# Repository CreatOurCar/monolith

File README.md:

# monolith

DIY data logging platform for Student Formula and Baja: ESP32-S3 firmware records sensors straight to an SD card, and recorded logs are analyzed on the external upstream site (https://v2.monolith.luftaquila.io/).

## Development Environment

- **Required ESP-IDF version: v6.0.1**
- Verify with `idf.py --version` before building.
- **Building with a different version may break the firmware — always use v6.0.1.**

## Features

* 💾 Firmware logs straight to SD — no WiFi, no server, no live telemetry link
   * GPS (NMEA GPRMC) sets the wall clock so recorded logs carry correct absolute time
   * Recorded `.log` files are analyzed on the external upstream site: https://v2.monolith.luftaquila.io/

* 📀 Up to 100 Hz data rate with various signals
   * 1x CAN 2.0(A/B)
   * 1x External GPS
   * 1x Internal 6-axis Accelerometer & Gyroscope
   * 4x Digital input channels
   * 8x Analog input channels

* 🍺 Fully Open-source & Open-hardware under the Beerware license

## Documentation

[Full documentation](https://github.com/CreatOurCar/monolith/tree/main/docs) for DIY and usage details.

## Others

The name of the project was inspired by Arthur C. Clark's novel `2001: A Space Odyssey`.

## Sponsors

### Individuals

<!-- sponsors --><!-- sponsors -->

## LICENSE

For non-commercial use only:

```
"THE BEERWARE LICENSE" (Revision 42):
LUFT-AQUILA wrote this project. As long as you retain this notice,
you can do whatever you want with this stuff. If we meet someday,
and you think this stuff is worth it, you can buy me a beer in return.
```

<br>

<picture>
  <source media="(prefers-color-scheme: dark)" srcset="https://api.star-history.com/svg?repos=CreatOurCar/monolith&type=Date&theme=dark" />
  <source media="(prefers-color-scheme: light)" srcset="https://api.star-history.com/svg?repos=CreatOurCar/monolith&type=Date" />
  
</picture>

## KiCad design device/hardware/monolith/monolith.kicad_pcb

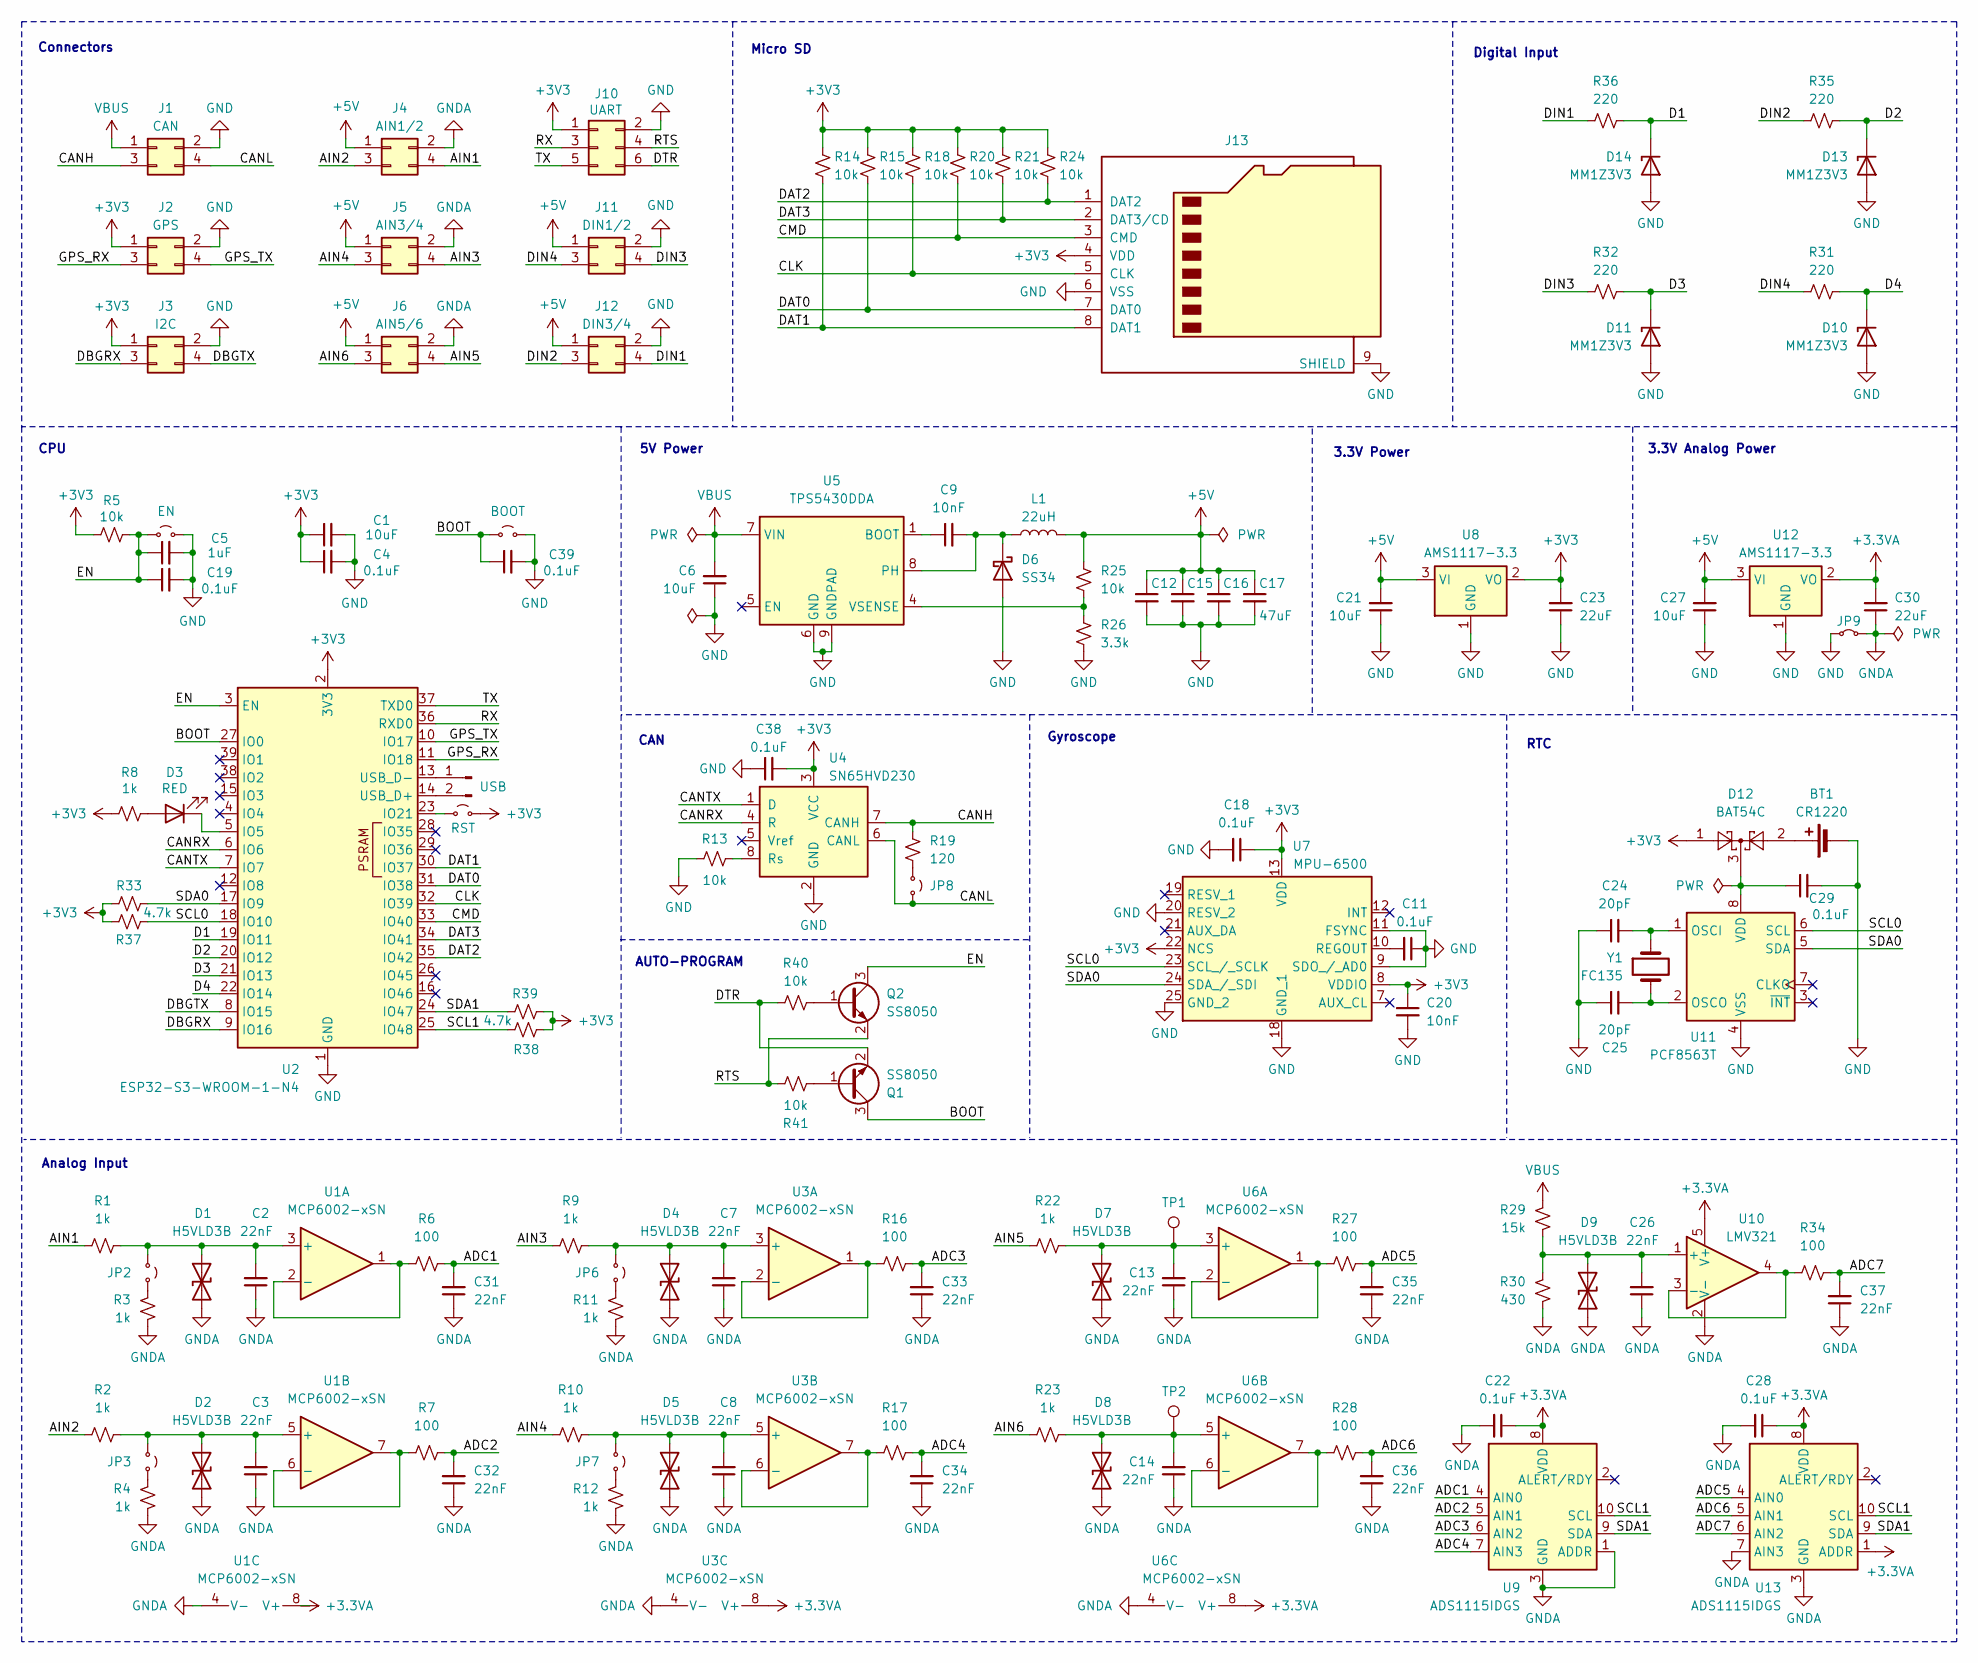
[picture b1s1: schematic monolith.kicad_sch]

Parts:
BT1: CR1220; S8411-45R_1; Manufacturer_Part_Number CR1220-2; LCSC C70381
C1, C21, C27: 10uF; C_0603_1608Metric; LCSC C19702
C2, C3, C7, C8, C13, C14, C26, C31, C32, C33, C34, C35, C36, C37: 22nF; C_0603_1608Metric; LCSC C21122
C4, C11, C18, C19, C22, C28, C29, C38, C39: 0.1uF; C_0603_1608Metric; LCSC C14663
C5: 1uF; C_0603_1608Metric; LCSC C15849
C6: 10uF; C_1206_3216Metric; LCSC C13585
C9, C20: 10nF; C_0603_1608Metric; LCSC C57112
C12, C15, C16, C17: 47uF; C_1206_3216Metric; LCSC C96123
C23, C30: 22uF; C_0603_1608Metric; LCSC C59461
C24, C25: 20pF; C_0603_1608Metric; LCSC C1648
D1, D2, D4, D5, D7, D8, D9: H5VLD3B; D_SOD-323; LCSC C20615805
D3: RED; LED_0603_1608Metric; LCSC C2286
D6: SS34; D_SMA; LCSC C8678
D10, D11, D13, D14: MM1Z3V3; D_SOD-123; LCSC C22379456
D12: BAT54C; SOT-23; Manufacturer_Part_Number BAT54C; LCSC C37704
J1: CAN; Molex_Mini-Fit_Jr_5569-04A2_2x02_P4.20mm_Horizontal
J2: GPS; Molex_Mini-Fit_Jr_5569-04A2_2x02_P4.20mm_Horizontal
J3: I2C; Molex_Mini-Fit_Jr_5569-04A2_2x02_P4.20mm_Horizontal
J4: AIN1/2; Molex_Mini-Fit_Jr_5569-04A2_2x02_P4.20mm_Horizontal
J5: AIN3/4; Molex_Mini-Fit_Jr_5569-04A2_2x02_P4.20mm_Horizontal
J6: AIN5/6; Molex_Mini-Fit_Jr_5569-04A2_2x02_P4.20mm_Horizontal
J7: USB; PinHeader_1x02_P1.00mm_Vertical
J10: UART; PinHeader_2x03_P2.54mm_Vertical
J11: DIN1/2; Molex_Mini-Fit_Jr_5569-04A2_2x02_P4.20mm_Horizontal
J12: DIN3/4; Molex_Mini-Fit_Jr_5569-04A2_2x02_P4.20mm_Horizontal
J13: Micro_SD_Card; TF115BCP9; LCSC C393941
JP1: EN; PinHeader_1x02_P1.00mm_Vertical
JP2, JP3, JP6, JP7: Jumper_2_Small_Open; PinHeader_1x02_P2.54mm_Vertical
JP4: BOOT; PinHeader_1x02_P1.00mm_Vertical
JP5: RST; PinHeader_1x02_P2.54mm_Vertical
JP8: CAN 120Ω; PinHeader_1x02_P2.54mm_Vertical
JP9: Jumper_2_Small_Bridged; SolderJumper-2_P1.3mm_Bridged_RoundedPad1.0x1.5mm
L1: 22uH; L_Sunlord_MWSA0603S; LCSC C177244
Q1, Q2: SS8050; SOT-23; LCSC C2150
R1, R2, R3, R4, R8, R9, R10, R11, R12, R22, R23: 1k; R_0603_1608Metric; LCSC C21190
R5, R13, R14, R15, R18, R20, R21, R24, R25, R40, R41: 10k; R_0603_1608Metric; LCSC C25804
R6, R7, R16, R17, R27, R28, R34: 100; R_0603_1608Metric; LCSC C22775
R19: 120; R_0603_1608Metric; LCSC C22787
R26: 3.3k; R_0603_1608Metric; LCSC C22978
R29: 15k; R_0603_1608Metric; LCSC C22809
R30: 430; R_0603_1608Metric; LCSC C23170
R31, R32, R35, R36: 220; R_0603_1608Metric; LCSC C22962
R33, R37, R38, R39: 4.7k; R_0603_1608Metric; LCSC C23162
TP1, TP2: TestPoint; PinHeader_1x01_P1.00mm_Vertical
U1, U3, U6: MCP6002-xSN; SOIC-8_3.9x4.9mm_P1.27mm; LCSC C7377
U2: ESP32-S3-WROOM-1-N4; ESP32-S3-WROOM-1; LCSC C2913197
U4: SN65HVD230; SOIC-8_3.9x4.9mm_P1.27mm; LCSC C12084
U5: TPS5430DDA; TI_SO-PowerPAD-8_ThermalVias; LCSC C9864
U7: MPU-6500; QFN40P300X300X95-25N-D; Manufacturer_Part_Number MPU-6500; Mouser Part Number 410-MPU-6500
U8, U12: AMS1117-3.3; SOT-223-3_TabPin2; LCSC C6186
U9, U13: ADS1115IDGS; TSSOP-10_3x3mm_P0.5mm; LCSC C37593
U10: LMV321; SOT-23-5; LCSC C7972
U11: PCF8563T; SOIC-8_3.9x4.9mm_P1.27mm; LCSC C7440
Y1: FC135; Crystal_SMD_3215-2Pin_3.2x1.5mm; LCSC C32346

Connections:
+3.3VA: C22.1, C28.1, C30.2, U1.8 (V+), U3.8 (V+), U6.8 (V+), U9.8 (VDD), U10.5 (V+), U12.2 (VO), U13.1 (ADDR), U13.8 (VDD)
+3V3: C1.1, C4.1, C18.1, C20.1, C23.2, C38.2, D12.1, J2.1, J3.1, J10.1, J13.4 (VDD), JP5.2 (B), R5.2, R8.1, R14.2, R15.2, R18.2, R20.2, R21.2, R24.2, R33.1, R37.2, R38.1, R39.2, U2.2 (3V3), U4.3 (VCC), U7.8 (VDDIO), U7.13 (VDD), U7.22 (NCS), U8.2 (VO)
+5V: C12.1, C15.1, C16.1, C17.1, C21.2, C27.2, J4.1, J5.1, J6.1, J11.1, J12.1, L1.2, R25.2, U8.3 (VI), U12.3 (VI)
/ADC1: C31.2, R6.2, U9.4 (AIN0)
/ADC2: C32.2, R7.2, U9.5 (AIN1)
/ADC3: C33.2, R16.2, U9.6 (AIN2)
/ADC4: C34.2, R17.2, U9.7 (AIN3)
/ADC5: C35.2, R27.2, U13.4 (AIN0)
/ADC6: C36.2, R28.2, U13.5 (AIN1)
/ADC7: C37.2, R34.2, U13.6 (AIN2)
/AIN1: J4.4, R1.1
/AIN2: J4.3, R2.1
/AIN3: J5.4, R9.1
/AIN4: J5.3, R10.1
/AIN5: J6.4, R22.1
/AIN6: J6.3, R23.1
/BOOT: C39.1, JP4.1 (A), Q1.3 (C), U2.27 (IO0)
/CANH: J1.3, R19.2, U4.7 (CANH)
/CANL: J1.4, JP8.2 (B), U4.6 (CANL)
/CANRX: U2.6 (IO6), U4.4 (R)
/CANTX: U2.7 (IO7), U4.1 (D)
/CLK: J13.5 (CLK), R18.1, U2.32 (IO39)
/CMD: J13.3 (CMD), R20.1, U2.33 (IO40)
/D1: D14.1 (K), R36.2, U2.19 (IO11)
/D2: D13.1 (K), R35.2, U2.20 (IO12)
/D3: D11.1 (K), R32.2, U2.21 (IO13)
/D4: D10.1 (K), R31.2, U2.22 (IO14)
/DAT0: J13.7 (DAT0), R15.1, U2.31 (IO38)
/DAT1: J13.8 (DAT1), R14.1, U2.30 (IO37)
/DAT2: J13.1 (DAT2), R24.1, U2.35 (IO42)
/DAT3: J13.2 (DAT3/CD), R21.1, U2.34 (IO41)
/DBGRX: J3.3, U2.9 (IO16)
/DBGTX: J3.4, U2.8 (IO15)
/DIN1: J12.4, R36.1
/DIN2: J12.3, R35.1
/DIN3: J11.4, R32.1
/DIN4: J11.3, R31.1
/DTR: J10.6, Q1.2 (E), R40.1
/EN: C5.1, C19.1, JP1.1 (A), Q2.3 (C), R5.1, U2.3 (EN)
/GPS_RX: J2.3, U2.11 (IO18)
/GPS_TX: J2.4, U2.10 (IO17)
/RTS: J10.4, Q2.2 (E), R41.2
/RX: J10.3, U2.36 (RXD0)
/SCL0: R37.1, U2.18 (IO10), U7.23 (SCL_/_SCLK), U11.6 (SCL)
/SCL1: R38.2, U2.25 (IO48), U9.10 (SCL), U13.10 (SCL)
/SDA0: R33.2, U2.17 (IO9), U7.24 (SDA_/_SDI), U11.5 (SDA)
/SDA1: R39.1, U2.24 (IO47), U9.9 (SDA), U13.9 (SDA)
/TX: J10.5, U2.37 (TXD0)
GND: BT1.2 (-), C1.2, C4.2, C5.2, C6.1, C11.1, C12.2, C15.2, C16.2, C17.2, C18.2, C19.2, C20.2, C21.1, C23.1, C24.1, C25.1, C27.1, C29.2, C38.1, C39.2, D6.2 (A), D10.2 (A), D11.2 (A), D13.2 (A), D14.2 (A), J1.2, J2.2, J3.2, J10.2, J11.2, J12.2, J13.6 (VSS), J13.9 (SHIELD), JP1.2 (B), JP4.2 (B), JP9.1 (A), R13.1, R26.1, U2.1 (GND), U2.40 (GND), U2.41 (GND), U4.2 (GND), U5.6 (GND), U5.9 (GNDPAD), U7.9 (SDO_/_AD0), U7.11 (FSYNC), U7.18 (GND_1), U7.20 (RESV_2), U7.25 (GND_2), U8.1 (GND), U11.4 (VSS), U12.1 (GND)
GNDA: C2.1, C3.1, C7.1, C8.1, C13.1, C14.1, C22.2, C26.1, C28.2, C30.1, C31.1, C32.1, C33.1, C34.1, C35.1, C36.1, C37.1, D1.2 (A2), D2.2 (A2), D4.2 (A2), D5.2 (A2), D7.2 (A2), D8.2 (A2), D9.2 (A2), J4.2, J5.2, J6.2, JP9.2 (B), R3.1, R4.1, R11.1, R12.1, R30.1, U1.4 (V-), U3.4 (V-), U6.4 (V-), U9.1 (ADDR), U9.3 (GND), U10.2 (V-), U13.3 (GND), U13.7 (AIN3)
unnamed: BT1.1 (+), D12.2
unnamed: C2.2, D1.1 (A1), JP2.1 (A), R1.2, U1.3 (+)
unnamed: C3.2, D2.1 (A1), JP3.1 (A), R2.2, U1.5 (+)
unnamed: D3.2 (A), R8.2
unnamed: D3.1 (K), U2.5 (IO5)
unnamed: C7.2, D4.1 (A1), JP6.1 (A), R9.2, U3.3 (+)
unnamed: C8.2, D5.1 (A1), JP7.1 (A), R10.2, U3.5 (+)
unnamed: C9.2, D6.1 (K), L1.1, U5.8 (PH)
unnamed: C13.2, D7.1 (A1), R22.2, TP1.1, U6.3 (+)
unnamed: C14.2, D8.1 (A1), R23.2, TP2.1, U6.5 (+)
unnamed: C26.2, D9.1 (A1), R29.1, R30.2, U10.1 (+)
unnamed: J7.1, U2.13 (USB_D-)
unnamed: J7.2, U2.14 (USB_D+)
unnamed: JP2.2 (B), R3.2
unnamed: JP3.2 (B), R4.2
unnamed: JP5.1 (A), U2.23 (IO21)
unnamed: JP6.2 (B), R11.2
unnamed: JP7.2 (B), R12.2
unnamed: JP8.1 (A), R19.1
unnamed: Q1.1 (B), R41.1
unnamed: Q2.1 (B), R40.2
unnamed: R6.1, U1.1, U1.2 (-)
unnamed: R7.1, U1.6 (-), U1.7
unnamed: R16.1, U3.1, U3.2 (-)
unnamed: R17.1, U3.6 (-), U3.7
unnamed: R13.2, U4.8 (Rs)
unnamed: C9.1, U5.1 (BOOT)
unnamed: R25.1, R26.2, U5.4 (VSENSE)
unnamed: R27.1, U6.1, U6.2 (-)
unnamed: R28.1, U6.6 (-), U6.7
unnamed: C11.2, U7.10 (REGOUT)
unnamed: R34.1, U10.3 (-), U10.4
unnamed: C24.2, U11.1 (OSCI), Y1.1
unnamed: C25.2, U11.2 (OSCO), Y1.2
unnamed: C29.1, D12.3, U11.8 (VDD)
VBUS: C6.2, J1.1, R29.2, U5.7 (VIN)

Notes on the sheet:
CAN
AUTO-PROGRAM
Analog Input
Micro SD
Digital Input
Connectors
3.3V Power
RTC
3.3V Analog Power
CPU
Gyroscope
5V Power

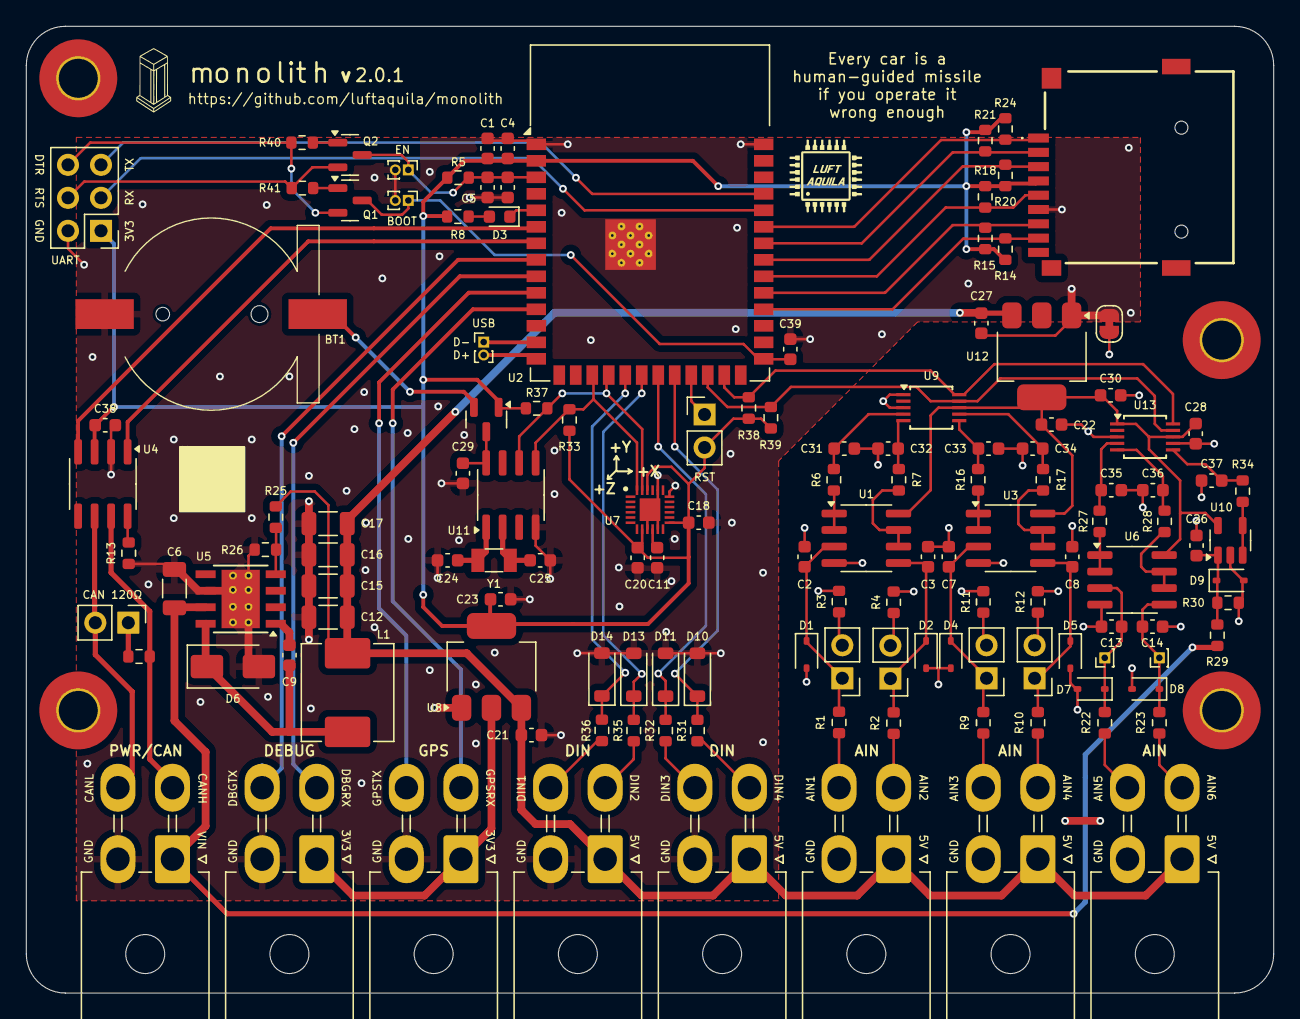
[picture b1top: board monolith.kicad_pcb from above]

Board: 2 copper layers, 96.0 x 74.4 mm, 133 parts (0 on the bottom side), 86 nets.

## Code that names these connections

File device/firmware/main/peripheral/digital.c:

#include "main.h"

#include "driver/gpio.h"

// 기계식 스위치는 한 번 눌러도 접점이 수 ms 동안 수십 번 튕긴다(채터링).
// 엣지마다 그대로 기록하면 로그 큐/SD가 쓰레기 레코드로 넘치므로:
//   ISR   — 마지막 엣지 시각만 남기고 태스크를 깨운다 (기록하지 않음)
//   task  — 버스트 첫 엣지에 즉시 1회 기록(지연 최소화), 이후 신호가
//           DEBOUNCE_QUIET_MS 동안 조용해지면 안정된 최종 상태를 기록
// 기록되는 레코드 자체는 기존과 동일한 4채널 상태 스냅샷 — 로그 형식 불변.
#define DEBOUNCE_QUIET_MS 10

static TaskHandle_t digital_task;
static volatile TickType_t last_edge_tick;  // 1kHz tick == 1ms; 32-bit write is atomic

static void digital_isr(void *arg) {
  last_edge_tick = xTaskGetTickCountFromISR();

  BaseType_t woken = pdFALSE;
  vTaskNotifyGiveFromISR(digital_task, &woken);
  portYIELD_FROM_ISR(woken);
}

/* read all four inputs; log only when the state differs from the last logged one */
static void digital_sample_and_log(bool force) {
  uint32_t din1 = gpio_get_level(GPIO_NUM_11);
  uint32_t din2 = gpio_get_level(GPIO_NUM_12);
  uint32_t din3 = gpio_get_level(GPIO_NUM_13);
  uint32_t din4 = gpio_get_level(GPIO_NUM_14);

  if (!force && logbuf.digital.payload.digital.din1 == din1 && logbuf.digital.payload.digital.din2 == din2 &&
      logbuf.digital.payload.digital.din3 == din3 && logbuf.digital.payload.digital.din4 == din4) {
    return;
  }

  logbuf.digital.payload.digital.din1 = din1;
  logbuf.digital.payload.digital.din2 = din2;
  logbuf.digital.payload.digital.din3 = din3;
  logbuf.digital.payload.digital.din4 = din4;
  LOG(LOG_TYPE_DIGITAL, &logbuf.digital);
}

/*******************************************************************************
 * Digital input interrupt monitor task
 ******************************************************************************/
void task_digital(void *pvParameters) {
  gpio_config_t gpio;

  gpio.pin_bit_mask = (1ULL << GPIO_NUM_11) | (1ULL << GPIO_NUM_12) | (1ULL << GPIO_NUM_13) | (1ULL << GPIO_NUM_14);
  gpio.mode         = GPIO_MODE_INPUT;
  gpio.intr_type    = GPIO_INTR_ANYEDGE;
  gpio.pull_up_en   = GPIO_PULLUP_DISABLE;
  gpio.pull_down_en = GPIO_PULLDOWN_ENABLE;

  if (gpio_config(&gpio) != ESP_OK) {
    ERROR_SYSLOG(&init, DIGITAL, "GPIO init failure", "DGT_INIT_FAIL");
  }

  // record initial state
  digital_sample_and_log(true);

  digital_task = xTaskGetCurrentTaskHandle();

  esp_err_t ret = gpio_isr_handler_add(GPIO_NUM_11, digital_isr, NULL);
  ret |= gpio_isr_handler_add(GPIO_NUM_12, digital_isr, NULL);
  ret |= gpio_isr_handler_add(GPIO_NUM_13, digital_isr, NULL);
  ret |= gpio_isr_handler_add(GPIO_NUM_14, digital_isr, NULL);

  if (ret != ESP_OK) {
    ERROR_SYSLOG(&init, DIGITAL, "GPIO isr install failure", "DGT_ISR_FAIL");
  }

  if (IS_OK(&init, DIGITAL)) {
    CLEAR_ALL(&logbuf.run, DIGITAL);
    SYSLOG("DGT_RDY");
  } else {
    COPY_STATE(&logbuf.run, &init, DIGITAL);
  }

  while (true) {
    ulTaskNotifyTake(pdTRUE, portMAX_DELAY);  // wait for the first edge of a burst

    digital_sample_and_log(false);

    // wait until the inputs have been quiet for DEBOUNCE_QUIET_MS
    while (xTaskGetTickCount() - last_edge_tick < pdMS_TO_TICKS(DEBOUNCE_QUIET_MS)) {
      vTaskDelay(pdMS_TO_TICKS(2));
    }

    // drop notifications accumulated during the burst, then log the settled state.
    // an edge arriving after this take sets the notification again, so the outer
    // loop reruns and no final state change is ever lost.
    ulTaskNotifyTake(pdTRUE, 0);
    digital_sample_and_log(false);
  }
}

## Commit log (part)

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2025-06-02 add: install guide
2025-07-01 add: v2 schematics and footprints
2025-07-01 remove: Rust firmware
2025-07-25 add: initial project
2025-07-25 update: apply beerware for non-commercial use only
2025-07-25 add: ci build workflow
2025-07-25 update: PCB prototype
2025-07-25 add: Makefile and wokwi simulation
2025-07-25 update: idf config options
2025-07-25 add: error handling system and NVS config management
2025-07-25 add: start peripheral tasks by nvs value
2025-07-25 update: I2C2 to I2C0
2025-07-25 add: log protocol
2025-07-25 update: replace MPU-6050 to MPU-6500
2025-07-25 impl: webserver with ap mode
2025-07-25 update: set core clock to 240MHz
2025-07-25 fix: enforce IDF_PATH
2025-07-25 add: log checksum calc and enqueue
2025-07-25 add: basic structure and initializations
2025-07-25 add: logo assets
2025-07-25 fix: misc bugs
2025-07-25 update: prototype PCB
2025-07-25 add: STA mode prototype
2025-07-25 improve: led and logging system
2025-07-25 add: sntp time sync
2025-07-25 impl: mqtt online check with LWT
2025-07-25 improve: embed text files
2025-07-25 fix: set flash size to 4MB for N4
2025-07-25 improve: unify nvs namespace
2025-07-25 update: clang-format PointerAlignment
2025-07-25 improve: make traefik container optional
2025-07-25 impl: SNTP time sync to RTC
2025-07-25 update: set mqtt ACL and authentication
2025-07-25 add: mqtt topic subscription handler structure
2025-07-25 fix: wrong marking TX/RX on the PCB
2025-07-25 update: disable runtime log level checks
2025-07-25 impl: mqtt set commands
2025-07-25 update: set proper ignores
2025-07-25 add: basic server architecture
2025-07-25 fix: wrong LED direction
2025-07-25 update: set hostname and mac on AP name
2025-07-25 add: mqtt prototype
2025-07-25 add: make config
2025-07-25 add: tz info on config
2025-07-25 improve: nvs handling
2025-07-25 update: set coreid as enum
2025-07-25 update: enable QIO, set upload and console baud to 921600
2025-07-25 improve: error state management
2025-07-25 update: set global logbuf and run state
2025-07-25 impl: mqtt cmd ls, del, get
2025-07-25 add: info messages
2025-07-25 update: drop node and set nginx
2025-07-25 improve: add reboot button on html
2025-07-25 update: use synchronous api on i2c transfer
2025-07-25 fix: wait next period on transfer failure too
2025-07-25 add: 1s period mqtt data publish
2025-07-25 improve: quit task after init and make period correct
2025-07-25 remove: wokwi simulation
2025-07-25 impl: analog record
2025-07-25 update: set optimization level to -O2
2025-07-25 fix: state shift bits
2025-07-25 impl: RST button reset NVS
2025-07-25 improve: separate files per peripherals
2025-07-25 fix: record initial digital state
2025-07-25 add: digital input prototype
2025-07-25 impl: CAN message receive
2025-07-25 update: rename evtgrp variables
2025-07-25 fix: sync log to sd card
2025-07-25 fix: ci build
2025-07-25 add: publish syslog to mqtt
2025-07-25 Squashed 'web/' content from commit 23bcf92
    git-subtree-dir: web
    git-subtree-split: 23bcf922ab1826953fc32f85a3b6693a8bce10cc
2025-07-25 update: set frontend template
2025-07-27 update: apply dark theme and purple color
2025-07-27 update: settings page layout
2025-07-27 update: set topbar, default theme and logo
2025-07-27 remove: unused views
2025-07-27 bump: vite
2025-07-27 add: uplot
2025-07-27 update: add sample uplot graph
2025-07-27 update: set style
2025-07-27 update: set responsive chart size sample
2025-07-28 update: set acl file mod
2025-07-28 add: protocol parser prototype
2025-07-28 impl: set NVS via mqtt
2025-07-28 add: refresh button
2025-07-28 update: set keepalive
2025-07-28 update: idf to v5.5
2025-07-29 update: disable retain except boot record
2025-07-29 update: add terminal console
2025-07-29 impl: state telemetry
2025-07-29 add: time tags on state
2025-07-29 update: add uptime and set mqtt rate to 500ms
2025-07-29 fix: client side checksum failure
2025-07-29 impl: usrevt transmit and digital card view
2025-07-30 update: add views setting page
2025-07-30 improve: misc configuration behavior
2025-07-30 update: rename views
2025-07-30 impl: file list and delete
2025-07-30 update: disable cfg publish on mqtt conn
2025-07-31 impl: file download
2025-07-31 fix: send default USREVT on empty send and add ack
2025-07-31 update: view control variable
2025-08-01 impl: analog chart
2025-08-01 impl: gyro chart
2025-08-01 add: current position button
2025-08-01 impl: digital telemetry
2025-08-01 add: map
2025-08-01 update: chart and card styles
2025-08-01 impl: chart dark theme
2025-08-01 update: skip current log file on ls and del/all
2025-08-01 impl: multiple axes with same split range
2025-08-01 update: hide points
2025-08-02 improve: checksum failure during analog measurement
2025-08-02 add: viewer prototype
2025-08-03 impl: load file
2025-08-03 impl: graph viewer
2025-08-04 impl: events
2025-08-04 improve: graph view
2025-08-04 fix: load map on both page
2025-08-05 impl: gps prototype with pattern detection interrupt
2025-08-06 impl: neo6m config cmd
2025-08-06 impl: parse GPRMC message
2025-08-06 impl: parse gps log on web
2025-08-06 impl: telemetry map viewer
2025-08-06 fix: refresh list on delete
2025-08-06 update: add gps speed graph
2025-08-06 impl: gps viewer
2025-08-06 improve: map aspect-ratio
2025-08-06 improve: prevent downloading on other client
2025-08-06 update: drop 115200 bps gps for stability
2025-08-06 improve: gps coord accuracy
2025-08-06 fix: download filtering
2025-08-06 update: map mark colors
2025-08-06 impl: viewer timelapse slider
2025-08-06 improve: add position display
2025-08-06 improve: retry on i2c failure
2025-08-07 update: add download speed measurement, make get ack QOS 1
2025-08-07 update: make slider precise
2025-08-07 update: set analog prio to 6, core affinity to lwip and mqtt task
2025-08-07 improve: gps checksum fail
2025-08-07 update: auto load configuration
2025-08-07 add: display card toggle
2025-08-07 add: unit management
2025-08-07 impl: analog ui config
2025-08-07 update: save views to localStorage
2025-08-08 update: dynamic unit in telemetry
2025-08-08 improve: auto color generator
2025-08-08 improve: generate chart scale from units
2025-08-08 add: loading messages
2025-08-08 fix: usrevt terminating null char
2025-08-09 impl: can decoder
2025-08-09 improve: cardview style
2025-08-09 update: misc styles
2025-08-09 update: add uplot zoom plugins
2025-08-09 improve: set gyro offset registers
2025-08-09 fix: data without gps
2025-08-09 impl: telemetry update interval config
2025-08-10 impl: can receive
2025-08-10 fix: reset gyro offset before calibrate
2025-08-10 impl: can message transmit
2025-08-10 improve: error recovery
2025-08-10 impl: can telemetry graph view
2025-08-10 impl: export cfg
2025-08-10 improve: remove digital value from views
2025-08-11 drop: geolocation button
2025-08-11 improve: gyro error recovery
2025-08-11 impl: import/reset ui cfg
2025-08-11 fix: wrong button operation
2025-08-11 update: npm package name
2025-08-11 fix: docker-compose
2025-08-11 fix: xterm import
2025-08-11 fix: single page application routing
2025-08-11 fix: reset prev alert
2025-08-12 add: white logo
2025-08-12 add: docs template
2025-08-12 update: build firmware only on change at CI
2025-08-12 update: build docs on web build
2025-08-12 fix: docs routing
2025-08-12 impl: viewer can data
2025-08-12 update: full firmware for flashing
2025-08-12 update: remove jumpers
    PCB v2.0.1
2025-08-12 update: docs template
2025-08-12 update: README
2025-08-12 add: workflows
2025-08-14 add: theme license to html
2025-08-18 fix: GPS buffer overflow and add bitrate detection
2025-08-19 add: documentation
2025-08-22 update: disable additional NMEA messages
2025-08-22 update: remove all task core affinities
2025-08-22 improve: read CAN RX fifo more efficiently
2025-08-24 improve: split time slot
2025-08-24 fix: log magic mismatch handling
2025-08-25 impl: CAN id hash table for telemetry
2025-08-25 update: change FreeRTOS ticks to 50 Hz
2025-08-25 update: enlarge log queue length
2025-08-25 update: docs
2025-08-26 update: add mini firmware build
2025-08-27 add: mini hardware
2025-08-28 update: misc pcb changes
2025-08-29 impl: mini analog task
2025-10-20 build(deps-dev): bump vite from 7.0.6 to 7.1.11 in /web
    Bumps [vite](https://github.com/vitejs/vite/tree/HEAD/packages/vite) from 7.0.6 to 7.1.11.
    - [Release notes](https://github.com/vitejs/vite/releases)
    - [Changelog](https://github.com/vitejs/vite/blob/main/packages/vite/CHANGELOG.md)
    - [Commits](https://github.com/vitejs/vite/commits/v7.1.11/packages/vite)
    ---
    updated-dependencies:
2025-11-10 update: readme sponsors
2025-11-10 Deploying to main from @ luftaquila/monolith@65aa01479936febd3e259b5cb4d91d847d5a2b51 🚀
2025-11-10 update: add sponsor review in docs
2026-01-13 fix: release workflow
2026-01-16 add: firmware flashing script
2026-01-16 build(deps-dev): bump js-yaml from 4.1.0 to 4.1.1 in /web
    Bumps [js-yaml](https://github.com/nodeca/js-yaml) from 4.1.0 to 4.1.1.
    - [Changelog](https://github.com/nodeca/js-yaml/blob/master/CHANGELOG.md)
    - [Commits](https://github.com/nodeca/js-yaml/compare/4.1.0...4.1.1)
    ---
    updated-dependencies:
    - dependency-name: js-yaml
2026-01-23 npm update
2026-01-23 bump: npm packages
2026-01-23 update: docs for difference between mini and original
2026-03-20 add: CLAUDE.md
2026-03-20 fix: full nginx config with dynamic DNS, access_log off, asset caching
2026-03-21 build(deps-dev): bump minimatch from 3.1.2 to 3.1.5 in /web
    Bumps [minimatch](https://github.com/isaacs/minimatch) from 3.1.2 to 3.1.5.
    - [Changelog](https://github.com/isaacs/minimatch/blob/main/changelog.md)
    - [Commits](https://github.com/isaacs/minimatch/compare/v3.1.2...v3.1.5)
    ---
    updated-dependencies:
    - dependency-name: minimatch
2026-03-21 build(deps-dev): bump flatted from 3.3.3 to 3.4.2 in /web
    Bumps [flatted](https://github.com/WebReflection/flatted) from 3.3.3 to 3.4.2.
    - [Commits](https://github.com/WebReflection/flatted/compare/v3.3.3...v3.4.2)
    ---
    updated-dependencies:
    - dependency-name: flatted
    dependency-version: 3.4.2
2026-03-26 build(deps): bump picomatch from 4.0.3 to 4.0.4 in /web
    Bumps [picomatch](https://github.com/micromatch/picomatch) from 4.0.3 to 4.0.4.
    - [Release notes](https://github.com/micromatch/picomatch/releases)
    - [Changelog](https://github.com/micromatch/picomatch/blob/master/CHANGELOG.md)
    - [Commits](https://github.com/micromatch/picomatch/compare/4.0.3...4.0.4)
    ---
    updated-dependencies:
2026-03-31 build(deps): bump yaml from 2.8.2 to 2.8.3 in /web
    Bumps [yaml](https://github.com/eemeli/yaml) from 2.8.2 to 2.8.3.
    - [Release notes](https://github.com/eemeli/yaml/releases)
    - [Commits](https://github.com/eemeli/yaml/compare/v2.8.2...v2.8.3)
    ---
    updated-dependencies:
    - dependency-name: yaml
2026-04-06 build(deps-dev): bump vite from 8.0.1 to 8.0.5 in /web
    Bumps [vite](https://github.com/vitejs/vite/tree/HEAD/packages/vite) from 8.0.1 to 8.0.5.
    - [Release notes](https://github.com/vitejs/vite/releases)
    - [Changelog](https://github.com/vitejs/vite/blob/main/packages/vite/CHANGELOG.md)
    - [Commits](https://github.com/vitejs/vite/commits/v8.0.5/packages/vite)
    ---
    updated-dependencies:
2026-05-06 build(deps): bump ip-address from 10.1.0 to 10.2.0 in /web
    Bumps [ip-address](https://github.com/beaugunderson/ip-address) from 10.1.0 to 10.2.0.
    - [Commits](https://github.com/beaugunderson/ip-address/commits)
    ---
    updated-dependencies:
    - dependency-name: ip-address
    dependency-version: 10.2.0
2026-05-06 build(deps-dev): bump postcss from 8.5.8 to 8.5.14 in /web
    Bumps [postcss](https://github.com/postcss/postcss) from 8.5.8 to 8.5.14.
    - [Release notes](https://github.com/postcss/postcss/releases)
    - [Changelog](https://github.com/postcss/postcss/blob/main/CHANGELOG.md)
    - [Commits](https://github.com/postcss/postcss/compare/8.5.8...8.5.14)
    ---
    updated-dependencies:
2026-06-02 feat: COC 브랜딩 적용 및 로컬 Mosquitto 연결
